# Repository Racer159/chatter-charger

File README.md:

# chatter-charger

> [!CAUTION]
> This repository is still very WIP.

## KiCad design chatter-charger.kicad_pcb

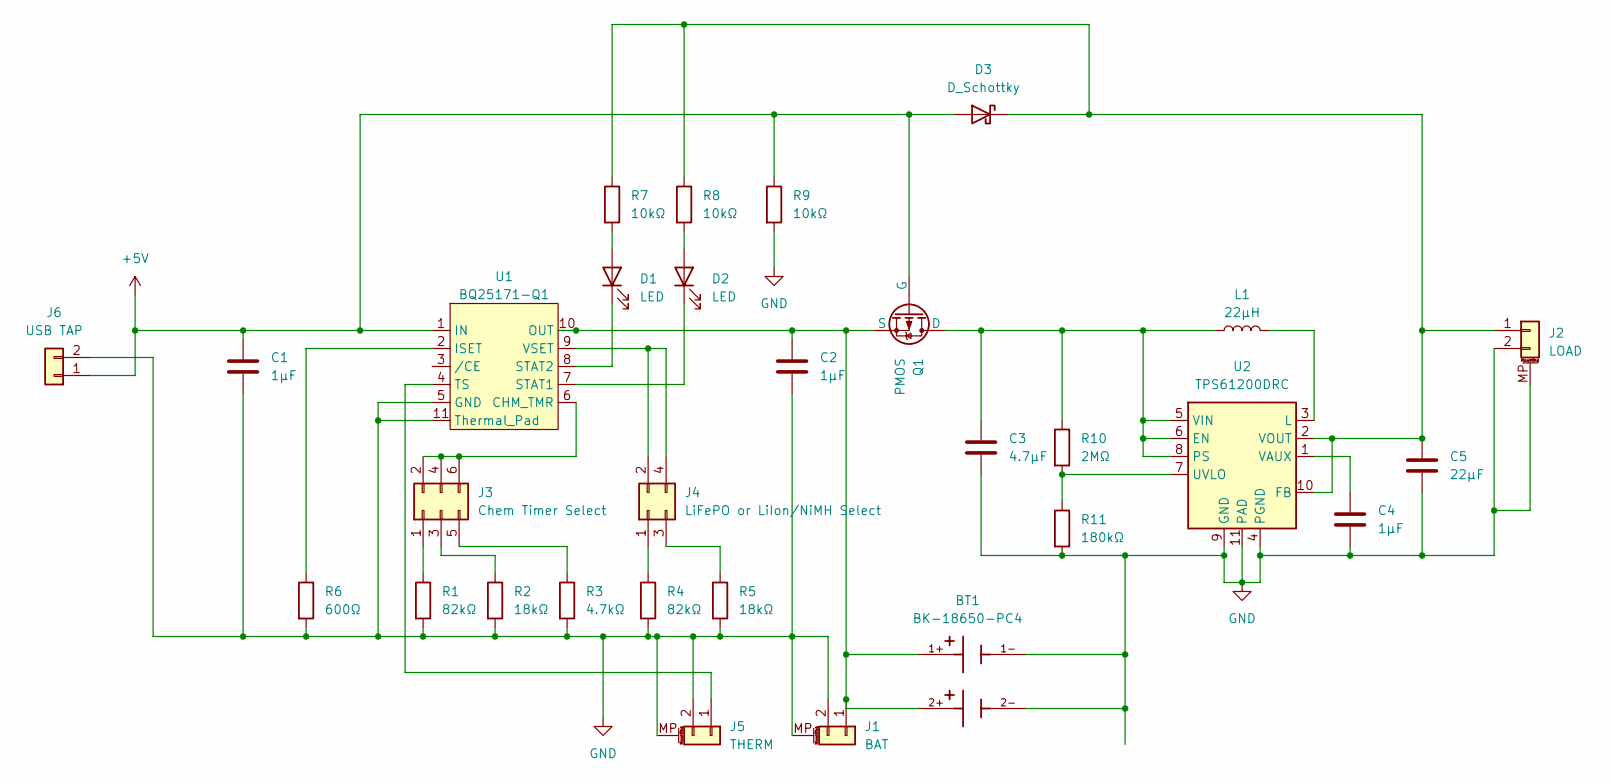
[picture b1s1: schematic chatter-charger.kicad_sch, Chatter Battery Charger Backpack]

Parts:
BT1: BK-18650-PC4; BAT_BK-18650-PC4; PARTREV K
C1, C2, C4: 1μF; C_0805_2012Metric_Pad1.18x1.45mm_HandSolder
C3: 4.7μF; C_0805_2012Metric_Pad1.18x1.45mm_HandSolder
C5: 22μF; C_0805_2012Metric_Pad1.18x1.45mm_HandSolder
D1, D2: LED; LED_0805_2012Metric_Pad1.15x1.40mm_HandSolder
D3: D_Schottky; D_0805_2012Metric_Pad1.15x1.40mm_HandSolder
J1: BAT; JST_PH_S2B-PH-SM4-TB_1x02-1MP_P2.00mm_Horizontal
J2: LOAD; JST_PH_S2B-PH-SM4-TB_1x02-1MP_P2.00mm_Horizontal
J3: Chem Timer Select; PinHeader_2x03_P2.00mm_Vertical_SMD
J4: LiFePO or LiIon/NiMH Select; PinHeader_2x02_P2.00mm_Vertical_SMD
J5: THERM; JST_PH_S2B-PH-SM4-TB_1x02-1MP_P2.00mm_Horizontal
J6: USB TAP; Chatter_USB_Tap
L1: 22μH; L_0805_2012Metric_Pad1.05x1.20mm_HandSolder
Q1: PMOS; SOT-23_Handsoldering
R1, R4: 82kΩ; R_0805_2012Metric_Pad1.20x1.40mm_HandSolder
R2, R5: 18kΩ; R_0805_2012Metric_Pad1.20x1.40mm_HandSolder
R3: 4.7kΩ; R_0805_2012Metric_Pad1.20x1.40mm_HandSolder
R6: 600Ω; R_0805_2012Metric_Pad1.20x1.40mm_HandSolder
R7, R8, R9: 10kΩ; R_0805_2012Metric_Pad1.20x1.40mm_HandSolder
R10: 2MΩ; R_0805_2012Metric_Pad1.20x1.40mm_HandSolder
R11: 180kΩ; R_0805_2012Metric_Pad1.20x1.40mm_HandSolder
U1: BQ25171-Q1; Texas_S-PVSON-N10_ThermalVias
U2: TPS61200DRC; Texas_S-PVSON-N10_ThermalVias

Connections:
+5V: C1.1, D3.2 (A), J6.1, Q1.2 (G), R9.1, U1.1 (IN)
GND: BT1.1-, BT1.2-, C1.2, C2.2, C3.2, C4.2, C5.2, J1.2, J1.MP (MountPin), J2.2, J2.MP (MountPin), J5.2, J5.MP (MountPin), J6.2, R1.2, R2.2, R3.2, R4.2, R5.2, R6.2, R9.2, R11.2, U1.5 (GND), U1.11 (Thermal_Pad), U2.4 (PGND), U2.9 (GND), U2.11 (PAD)
unnamed: D1.2 (A), R7.2
unnamed: D1.1 (K), U1.8 (STAT2)
unnamed: D2.2 (A), R8.2
unnamed: D2.1 (K), U1.7 (STAT1)
unnamed: C5.1, D3.1 (K), J2.1, R7.1, R8.1, U2.2 (VOUT), U2.10 (FB)
unnamed: BT1.1+, BT1.2+, C2.1, J1.1, Q1.3 (S), U1.10 (OUT)
unnamed: J3.1, R1.1
unnamed: J3.2, J3.4, J3.6, U1.6 (CHM_TMR)
unnamed: J3.3, R2.1
unnamed: J3.5, R3.1
unnamed: J4.1, R4.1
unnamed: J4.2, J4.4, U1.9 (VSET)
unnamed: J4.3, R5.1
unnamed: J5.1, U1.4 (TS)
unnamed: C3.1, L1.1, Q1.1 (D), R10.1, U2.5 (VIN), U2.6 (EN), U2.8 (PS)
unnamed: R6.1, U1.2 (ISET)
unnamed: L1.2, U2.3 (L)
unnamed: R10.2, R11.1, U2.7 (UVLO)
unnamed: C4.1, U2.1 (VAUX)

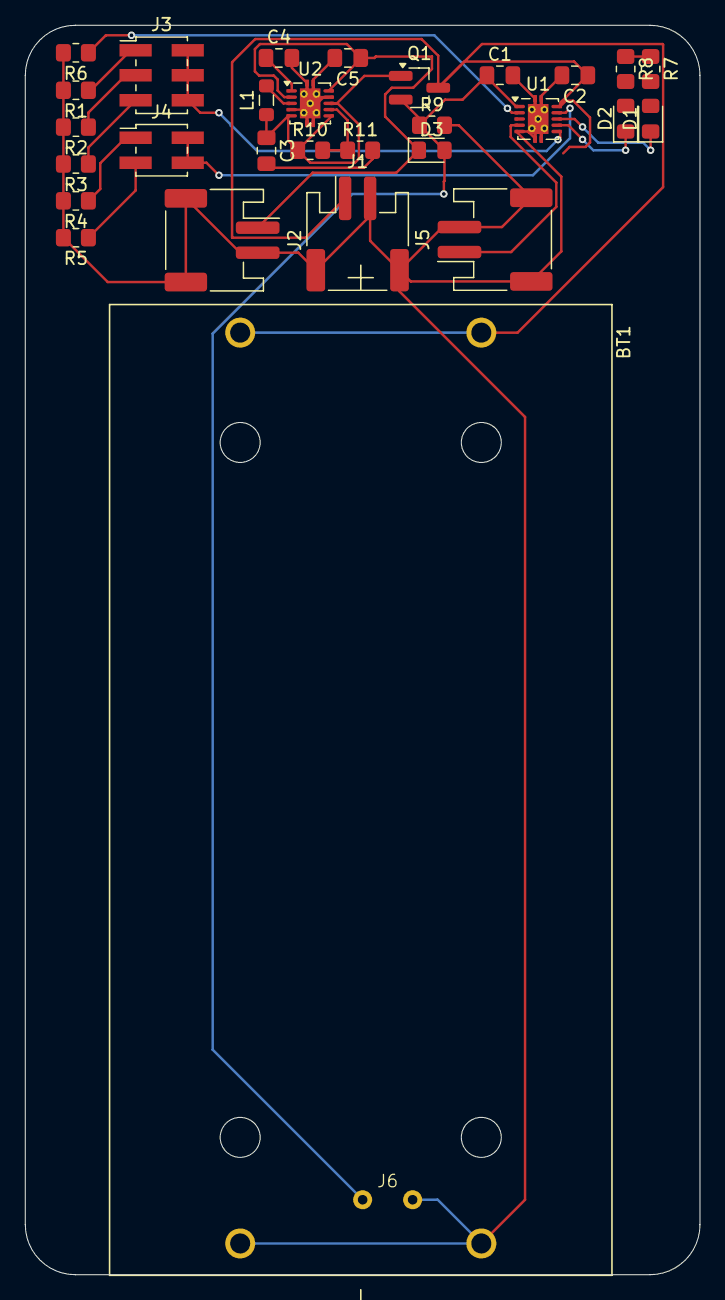
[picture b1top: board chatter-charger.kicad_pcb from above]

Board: 2 copper layers, 54.0 x 100.0 mm, 30 parts (0 on the bottom side), 21 nets.

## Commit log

2024-10-26 feat: initial commit into repo
